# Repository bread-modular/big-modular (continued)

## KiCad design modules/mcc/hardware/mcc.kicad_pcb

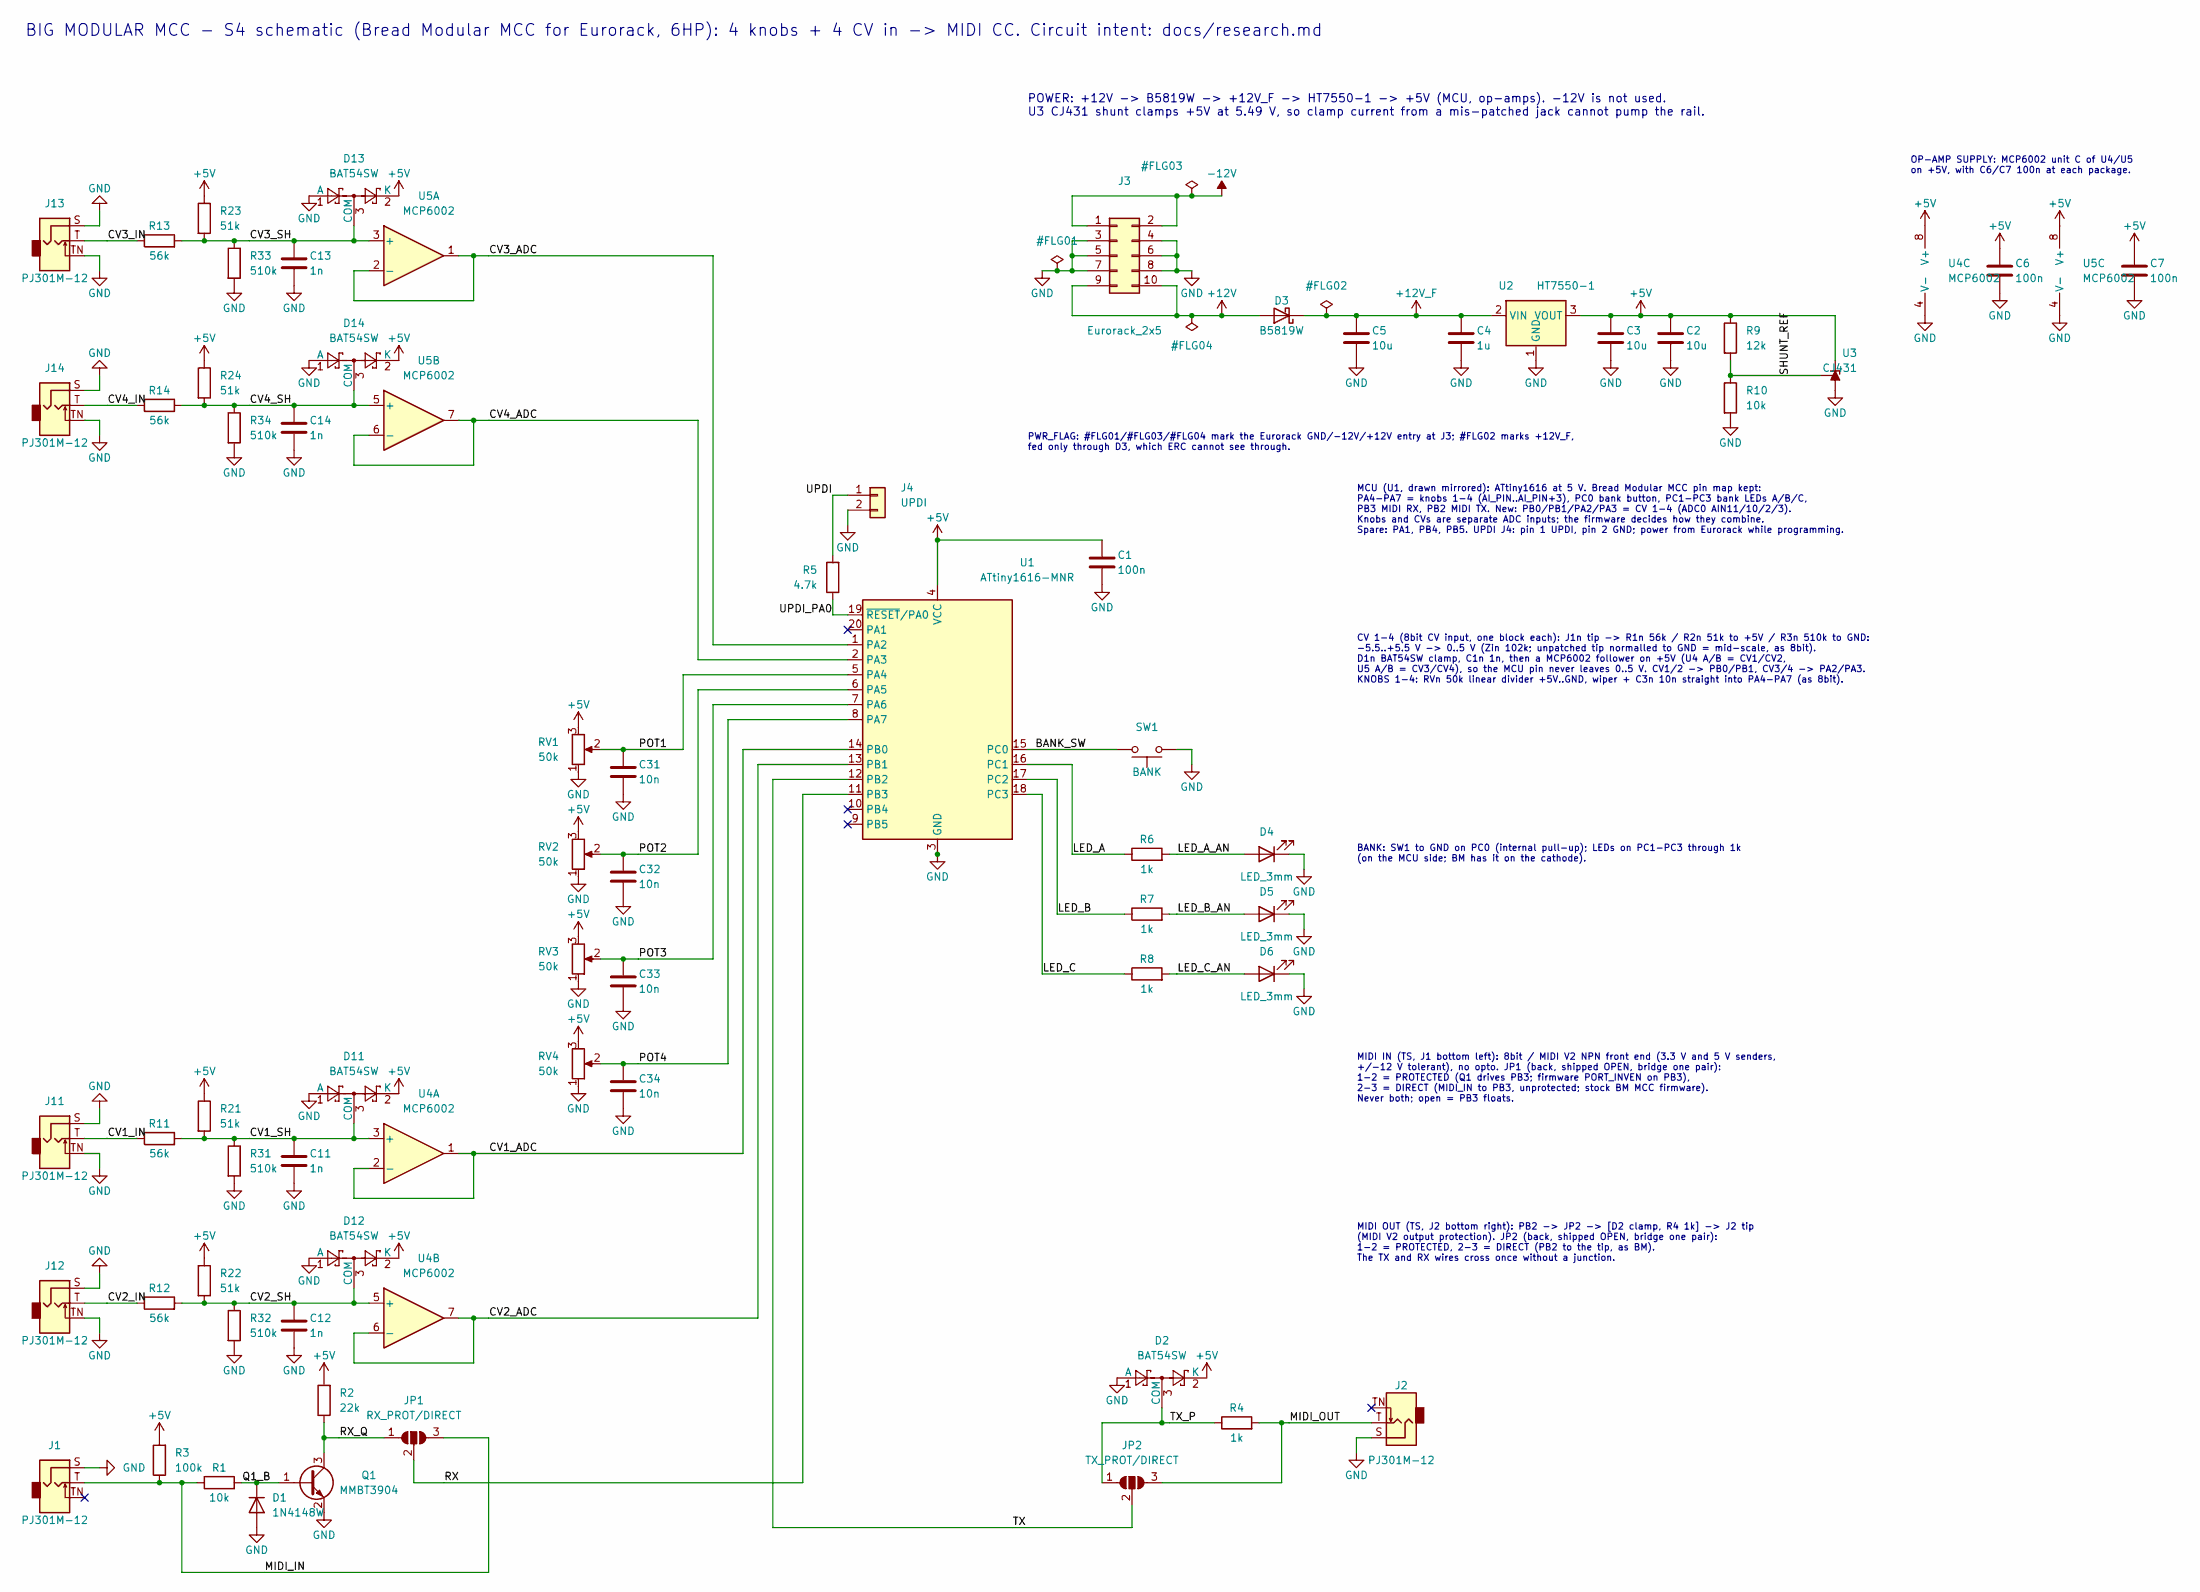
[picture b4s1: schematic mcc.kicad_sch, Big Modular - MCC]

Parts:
C1, C6, C7: 100n; C_0603_1608Metric; Voltage 50V; MPN CC0603KRX7R9BB104; LCSC C14663
C2, C3, C5: 10u; C_0805_2012Metric; Voltage 25V; MPN CL21A106KAYNNNE; LCSC C15850
C4: 1u; C_0805_2012Metric; Voltage 50V; MPN CL21B105KBFNNNE; LCSC C28323
C11, C12, C13, C14: 1n; C_0603_1608Metric; Voltage 50V; MPN CL10B102KB8NNNC; LCSC C1588
C31, C32, C33, C34: 10n; C_0603_1608Metric; Voltage 50V; MPN 0603B103K500NT; LCSC C57112
D1: 1N4148W; D_SOD-123; MPN 1N4148W; LCSC C81598
D2, D11, D12, D13, D14: BAT54SW; SOT-323_SC-70; MPN BAT54SWT1G; LCSC C78260
D3: B5819W; D_SOD-123; MPN B5819W SL; LCSC C8598
D4, D5, D6: LED_3mm; LED_D3.0mm
J1, J2, J11, J12, J13, J14: PJ301M-12; Jack_3.5mm_QingPu_WQP-PJ301M-12_Vertical
J3: Eurorack_2x5; PinHeader_2x05_P2.54mm_Vertical
J4: UPDI; PinHeader_1x02_P2.54mm_Vertical
JP1: RX_PROT/DIRECT; SolderJumper-3_P1.3mm_Open_RoundedPad1.0x1.5mm
JP2: TX_PROT/DIRECT; SolderJumper-3_P1.3mm_Open_RoundedPad1.0x1.5mm
Q1: MMBT3904; SOT-23; MPN MMBT3904(RANGE:100-300); LCSC C20526
R1, R10: 10k; R_0603_1608Metric; MPN 0603WAF1002T5E; LCSC C25804
R2: 22k; R_0603_1608Metric; MPN 0603WAF2202T5E; LCSC C31850
R3: 100k; R_0603_1608Metric; MPN 0603WAF1003T5E; LCSC C25803
R4: 1k; R_1206_3216Metric; MPN ESR18EZPF1001; LCSC C2074262
R5: 4.7k; R_0603_1608Metric; MPN 0603WAF4701T5E; LCSC C23162
R6, R7, R8: 1k; R_0603_1608Metric; MPN 0603WAF1001T5E; LCSC C21190
R9: 12k; R_0603_1608Metric; MPN 0603WAF1202T5E; LCSC C22790
R11, R12, R13, R14: 56k; R_0603_1608Metric; MPN 0603WAF5602T5E; LCSC C23206
R21, R22, R23, R24: 51k; R_0603_1608Metric; MPN 0603WAF5102T5E; LCSC C23196
R31, R32, R33, R34: 510k; R_0603_1608Metric; MPN 0603WAF5103T5E; LCSC C23192
RV1, RV2, RV3, RV4: 50k; Potentiometer_RV09
SW1: BANK; SW_PUSH_6mm_H7.3mm; MPN 6x6x7 mm THT tact switch, 4 pins (gener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
U1: ATtiny1616-MNR; VQFN-20-1EP_3x3mm_P0.4mm_EP1.7x1.7mm; MPN ATTINY1616-MNR; LCSC C507118
U2: HT7550-1; SOT-89-3; MPN HT7550-1; LCSC C16106
U3: CJ431; SOT-23; MPN CJ431; LCSC C3113
U4, U5: MCP6002; SOIC-8_3.9x4.9mm_P1.27mm; MPN MCP6002T-I/SN; LCSC C7377

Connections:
+5V: C1.1, C2.1, C3.1, C6.1, C7.1, D2.2 (K), D11.2 (K), D12.2 (K), D13.2 (K), D14.2 (K), R2.2, R3.2, R9.1, R21.1, R22.1, R23.1, R24.1, RV1.3, RV2.3, RV3.3, RV4.3, U1.4 (VCC), U2.3 (VOUT), U3.2 (K), U4.8 (V+), U5.8 (V+)
+12V: D3.2 (A), J3.9, J3.10
+12V_F: C4.1, C5.1, D3.1 (K), U2.2 (VIN)
-12V: J3.1, J3.2
/BANK_SW: SW1.2, U1.15 (PC0)
/CV1_ADC: U1.14 (PB0), U4.1, U4.2 (-)
/CV1_IN: J11.T, R11.1
/CV1_SH: C11.1, D11.3 (COM), R11.2, R21.2, R31.1, U4.3 (+)
/CV2_ADC: U1.13 (PB1), U4.6 (-), U4.7
/CV2_IN: J12.T, R12.1
/CV2_SH: C12.1, D12.3 (COM), R12.2, R22.2, R32.1, U4.5 (+)
/CV3_ADC: U1.1 (PA2), U5.1, U5.2 (-)
/CV3_IN: J13.T, R13.1
/CV3_SH: C13.1, D13.3 (COM), R13.2, R23.2, R33.1, U5.3 (+)
/CV4_ADC: U1.2 (PA3), U5.6 (-), U5.7
/CV4_IN: J14.T, R14.1
/CV4_SH: C14.1, D14.3 (COM), R14.2, R24.2, R34.1, U5.5 (+)
/LED_A: R6.1, U1.16 (PC1)
/LED_A_AN: D4.2 (A), R6.2
/LED_B: R7.1, U1.17 (PC2)
/LED_B_AN: D5.2 (A), R7.2
/LED_C: R8.1, U1.18 (PC3)
/LED_C_AN: D6.2 (A), R8.2
/MIDI_IN: J1.T, JP1.3 (B), R1.1, R3.1
/MIDI_OUT: J2.T, JP2.3 (B), R4.2
/POT1: C31.1, RV1.2, U1.5 (PA4)
/POT2: C32.1, RV2.2, U1.6 (PA5)
/POT3: C33.1, RV3.2, U1.7 (PA6)
/POT4: C34.1, RV4.2, U1.8 (PA7)
/Q1_B: D1.1 (K), Q1.1 (B), R1.2
/RX: JP1.2 (C), U1.11 (PB3)
/RX_Q: JP1.1 (A), Q1.3 (C), R2.1
/SHUNT_REF: R9.2, R10.1, U3.1 (REF)
/TX: JP2.2 (C), U1.12 (PB2)
/TX_P: D2.3 (COM), JP2.1 (A), R4.1
/UPDI: J4.1, R5.2
/UPDI_PA0: R5.1, U1.19 (~RESET/PA0)
GND: C1.2, C2.2, C3.2, C4.2, C5.2, C6.2, C7.2, C11.2, C12.2, C13.2, C14.2, C31.2, C32.2, C33.2, C34.2, D1.2 (A), D2.1 (A), D4.1 (K), D5.1 (K), D6.1 (K), D11.1 (A), D12.1 (A), D13.1 (A), D14.1 (A), J1.S, J2.S, J3.3, J3.4, J3.5, J3.6, J3.7, J3.8, J4.2, J11.S, J11.TN, J12.S, J12.TN, J13.S, J13.TN, J14.S, J14.TN, Q1.2 (E), R10.2, R31.2, R32.2, R33.2, R34.2, RV1.1, RV2.1, RV3.1, RV4.1, SW1.1, U1.3 (GND), U1.21 (GND), U2.1 (GND), U3.3 (A), U4.4 (V-), U5.4 (V-)

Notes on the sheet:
MIDI IN (TS, J1 bottom left): 8bit / MIDI V2 NPN front end (3.3 V and 5 V senders, +/-12 V tolerant), no opto. JP1 (back, shipped OPEN, bridge one pair): 1-2 = PROTECTED (Q1 drives PB3; firmware PORT_INVEN on PB3), 2-3 = DIRECT (MIDI_IN to PB3, unprotected; stock BM MCC firmware). Never both; open 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
BANK: SW1 to GND on PC0 (internal pull-up); LEDs on PC1-PC3 through 1k (on the MCU side; BM has it on the cathode).
MIDI OUT (TS, J2 bottom right): PB2 -> JP2 -> [D2 clamp, R4 1k] -> J2 tip (MIDI V2 output protection). JP2 (back, shipped OPEN, bridge one pair): 1-2 = PROTECTED, 2-3 = DIRECT (PB2 to the tip, as BM). The TX and RX wires cross once without a junction.
BIG MODULAR MCC - S4 schematic (Bread Modular MCC for Eurorack, 6HP): 4 knobs + 4 CV in -> MIDI CC. Circuit intent: docs/research.md
OP-AMP SUPPLY: MCP6002 unit C of U4/U5 on +5V, with C6/C7 100n at each package.
POWER: +12V -> B5819W -> +12V_F -> HT7550-1 -> +5V (MCU, op-amps). -12V is not used. U3 CJ431 shunt clamps +5V at 5.49 V, so clamp current from a mis-patched jack cannot pump the rail.
MCU (U1, drawn mirrored): ATtiny1616 at 5 V. Bread Modular MCC pin map kept: PA4-PA7 = knobs 1-4 (AI_PIN..AI_PIN+3), PC0 bank button, PC1-PC3 bank LEDs A/B/C, PB3 MIDI RX, PB2 MIDI TX. New: PB0/PB1/PA2/PA3 = CV 1-4 (ADC0 AIN11/10/2/3). Knobs and CVs are separate ADC inputs; the firmware decides how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
PWR_FLAG: #FLG01/#FLG03/#FLG04 mark the Eurorack GND/-12V/+12V entry at J3; #FLG02 marks +12V_F, fed only through D3, which ERC cannot see through.
CV 1-4 (8bit CV input, one block each): J1n tip -> R1n 56k / R2n 51k to +5V / R3n 510k to GND: -5.5..+5.5 V -> 0..5 V (Zin 102k; unpatched tip normalled to GND = mid-scale, as 8bit). D1n BAT54SW clamp, C1n 1n, then a MCP6002 follower on +5V (U4 A/B = CV1/CV2, U5 A/B = CV3/CV4), so the MCU pin never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

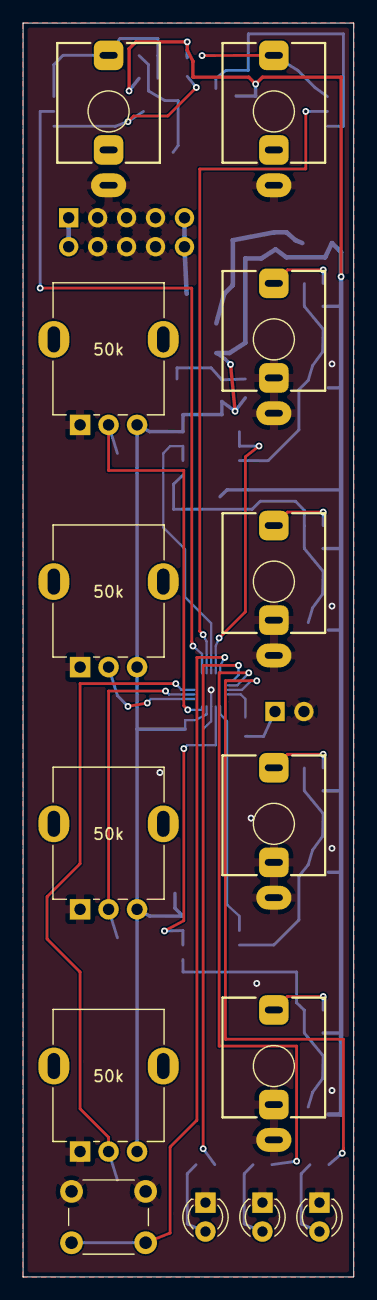
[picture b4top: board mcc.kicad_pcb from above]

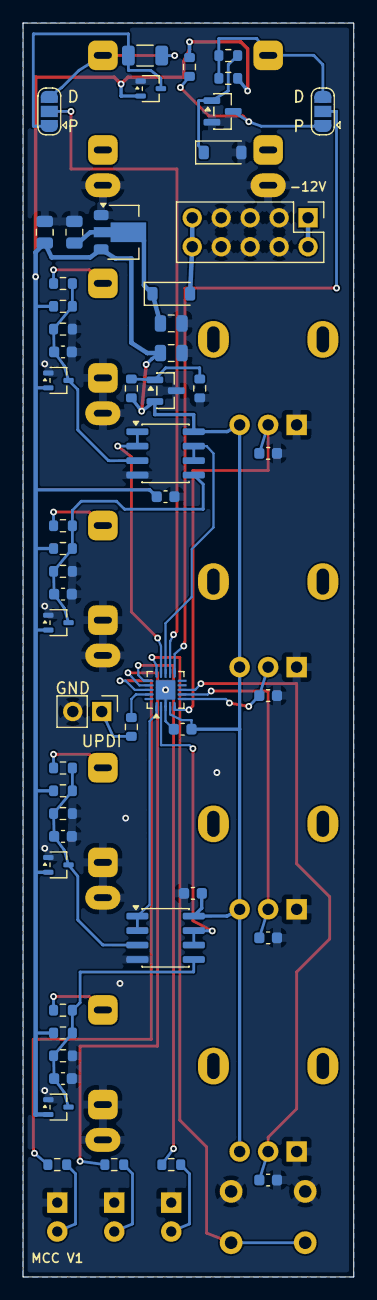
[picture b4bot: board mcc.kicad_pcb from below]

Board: 2 copper layers, 29.0 x 110.0 mm, 68 parts (54 on the bottom side), 38 nets.
